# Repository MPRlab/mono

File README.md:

MPR_WORKSPACE
=============

This repository, for the most part, is licensed under GPL V3.0.  This includes any code inside ipython notebooks.  A copy of the GPL V3.0 is available in the file license.txt

This repository is intended to store all code development for the Music Perception and Robotics Lab at WPI.

Currently, it is divided into several different directories:

Old Work:

AudioAnalysis - used for development of a real time pitch and onset detection system

MessagePassing - Test code for message passing via sockets

SharedMemoryTest - Test code for shared memory structure eventually used for leap motion controller

oscpack_1_1_0 - Library code to use for OSC (should have installation code maybe?)

build - All exectuables produced 

New Work:

Algorithmic_Composition_Tools - a directory to place general scripts and tools, like pitch number to western music notation or pitch number to midi output.  

Composition_Workspace_Hughes - Nathan's directory for path planning algorithms and C-Space generator / collision checker

Daughter_Control - directory for eventual software for instrument controllers

Mother_Control - directory for eventual software for motherboard controller

MAX_MSP_MIDI_CONVERTER - max/msp plugin for converting midi to custom osc messages

PAM_CONTROL - directory for old code / test code for pam

PERCUSSION_CONTROL - directory for old code / test code for percussion robot

MISC_DOC - directory for anything that doesn't belong

It also includes the following files:

Makefile - file to make programs from the various directories

README.md - this file

Please note that this repo is very much in progress. Some things that need to be done are the following (but are not limited to)
1) Document current Executables
2) Add Max/MXP plugins to the repo
3) Look into better build system than make

Finally, this repo has programs in a few different langauges and a couple different dependencies.

Languages: C, C++, Python
Dependencies: Jackd (audio analysis), boost (everything), ipython and numpy and scipy (some experimental audio analysis)

The dependencies is not an exhaustive list.  If a program doesn't run, it's probably missing a dependency.
=======
# MPR-lab

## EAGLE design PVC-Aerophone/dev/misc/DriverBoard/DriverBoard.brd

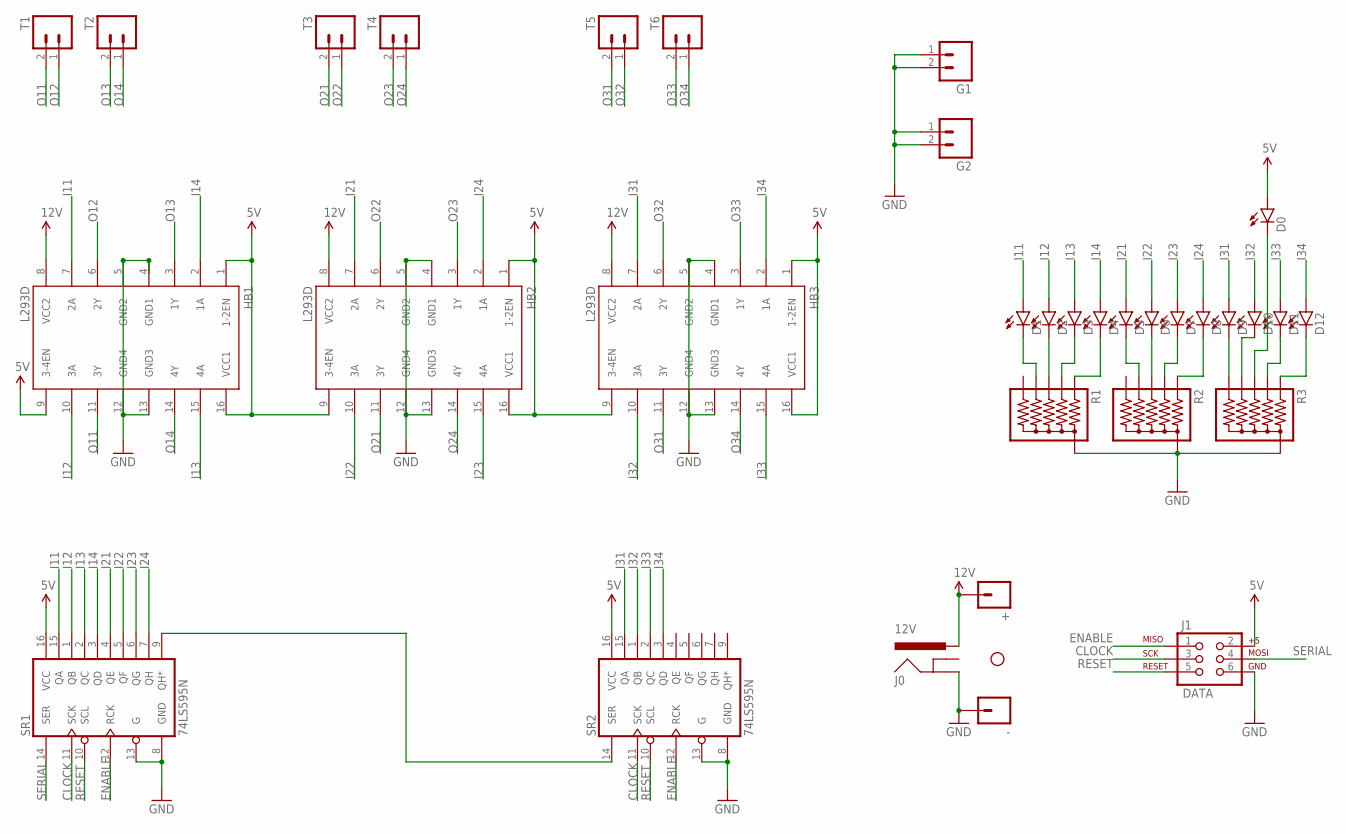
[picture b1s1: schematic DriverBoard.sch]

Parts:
+: M01PTH_NO_SILK_YES_STOP; 1X01_NO_SILK
-: M01PTH_NO_SILK_YES_STOP; 1X01_NO_SILK
D0, D1, D2, D3, D4, D5, D6, D7, D8, D9, D10, D11, D12: LED5MM
G1, G2: M025MM; SCREWTERMINAL-5MM-2
H1: STAND-OFF
HB1, HB2, HB3: L293D; DIL16
J0: 12V; POWER_JACK_PTH_BREAD
J1: DATA; 2X3
R1, R2, R3: RPACK-BUSSED-5-SIP-PTH-5; RPACK-SIP-PTH-5
SR1, SR2: 74LS595N; DIL16
T1, T2, T3, T4, T5, T6: M025MM; SCREWTERMINAL-5MM-2

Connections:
5V: D0.A, HB1.1 (1-2EN), HB1.9 (3-4EN), HB1.16 (VCC1), HB2.1 (1-2EN), HB2.9 (3-4EN), HB2.16 (VCC1), HB3.1 (1-2EN), HB3.9 (3-4EN), HB3.16 (VCC1), J1.2, SR1.16 (VCC), SR2.16 (VCC)
12V: +.1, HB1.8 (VCC2), HB2.8 (VCC2), HB3.8 (VCC2), J0.PWR
CLOCK: J1.3, SR1.11 (SCK), SR2.11 (SCK)
ENABLE: J1.1, SR1.12 (RCK), SR2.12 (RCK)
GND: -.1, G1.1, G1.2, G2.1, G2.2, HB1.4 (GND1), HB1.5 (GND2), HB1.12 (GND4), HB1.13 (GND3), HB2.4 (GND1), HB2.5 (GND2), HB2.12 (GND4), HB2.13 (GND3), HB3.4 (GND1), HB3.5 (GND2), HB3.12 (GND4), HB3.13 (GND3), J0.GND, J1.6, R1.P$1 (1), R2.P$1 (1), R3.P$1 (1), SR1.8 (GND), SR1.13 (G), SR2.8 (GND), SR2.13 (G)
I11: D1.A, HB1.7 (2A), SR1.15 (QA)
I12: D2.A, HB1.10 (3A), SR1.1 (QB)
I13: D3.A, HB1.15 (4A), SR1.2 (QC)
I14: D4.A, HB1.2 (1A), SR1.3 (QD)
I21: D5.A, HB2.7 (2A), SR1.4 (QE)
I22: D6.A, HB2.10 (3A), SR1.5 (QF)
I23: D7.A, HB2.15 (4A), SR1.6 (QG)
I24: D8.A, HB2.2 (1A), SR1.7 (QH)
I31: D9.A, HB3.7 (2A), SR2.15 (QA)
I32: D10.A, HB3.10 (3A), SR2.1 (QB)
I33: D11.A, HB3.15 (4A), SR2.2 (QC)
I34: D12.A, HB3.2 (1A), SR2.3 (QD)
unnamed: D10.K (C), R3.P$5 (5)
unnamed: D0.K (C), R3.P$4 (4)
unnamed: D4.K (C), R1.P$2 (2)
unnamed: D3.K (C), R1.P$3 (3)
unnamed: D2.K (C), R1.P$4 (4)
unnamed: D1.K (C), R1.P$5 (5)
unnamed: D8.K (C), R2.P$2 (2)
unnamed: D7.K (C), R2.P$3 (3)
unnamed: D6.K (C), R2.P$4 (4)
unnamed: D5.K (C), R2.P$5 (5)
unnamed: D12.K (C), R3.P$2 (2)
unnamed: D11.K (C), R3.P$3 (3)
unnamed: D9.K (C), R3.P$6 (6)
unnamed: SR1.9 (QH*), SR2.14 (SER)
O11: HB1.11 (3Y), T1.2
O12: HB1.6 (2Y), T1.1
O13: HB1.3 (1Y), T2.2
O14: HB1.14 (4Y), T2.1
O21: HB2.11 (3Y), T3.2
O22: HB2.6 (2Y), T3.1
O23: HB2.3 (1Y), T4.2
O24: HB2.14 (4Y), T4.1
O31: HB3.11 (3Y), T5.2
O32: HB3.6 (2Y), T5.1
O33: HB3.3 (1Y), T6.2
O34: HB3.14 (4Y), T6.1
RESET: J1.5, SR1.10 (SCL), SR2.10 (SCL)
SERIAL: J1.4, SR1.14 (SER)

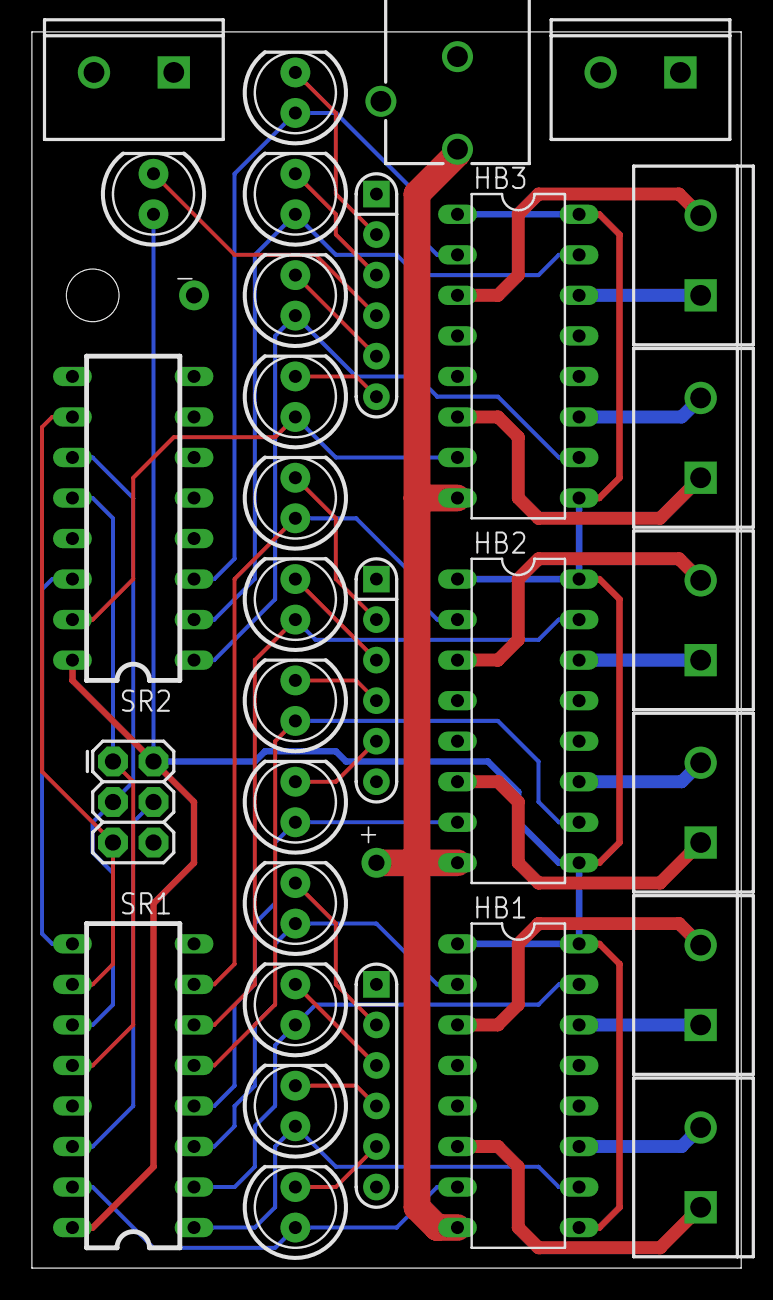
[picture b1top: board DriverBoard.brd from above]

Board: 2 copper layers, 44.5 x 77.5 mm, 34 parts (0 on the bottom side), 45 nets.

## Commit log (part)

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2015-02-25 More complex composition and MAX patch now allows for file to be input more easily
2015-02-25 Interesting composition. Good use of pauses. Better rhyth. Current adding register counting to the code.
2015-02-25 Still having problems exploring register diversity.
2015-02-25 Fixed problems with Airy inclusion. Still noticing some problems with repeated notes. Likely to be related to lack of forward checking in special cases.
2015-02-26 More complex composition. Better use of registers and rhyth. Fixed several bugs with code.
2015-02-26 Much more interesting composition. Added ability to control seed directly from file
2015-02-26 Added ability to choose gaussian distribution. Another composition created.
2015-02-26 Latest composition. Code seems to be fully functional.
2015-03-01 first draft of driver board
2015-03-01 test version that compiles
2015-03-03 transfered changes over to clean clone of repo
2015-03-03 added in proper pitch probabilites
2015-03-03 everything for class today
2015-03-30 starting code for OSC interface between pi and computer
2015-04-04 First push of the complete code for controlling the multi solenoid driver board V1 over serial. OOP. Tested on FluteBot and works for simple header 0x10 with pulse and hold.
2015-04-04 Added a class to control the high current solenoid driver. Code compiles.
2015-04-04 Added two new headers to control the power solenoid.
2015-04-05 New sample song added. Code now parses file and determines which solenoids should be active at any given time appropriately. Works still has to be done to transmit the messages over serial.
2015-04-06 Code is completed. However, has not been tested since it requires the board.
2015-04-06 README file added
2015-04-06 Code should be working. Mapping to solenoids has not been tested.
2015-04-06 Code has a major bug on the serial comparison that impedes serial from sending nonstop. Has been patched but has to be fixed ASAP.
2015-04-07 Changed the sending logic. Such that it now depends on a variable in status class providing proper separation between the com and status class. Also added a last send after song completion to turn of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
2015-04-07 Fixed bug where solenoids would be left ON after completion of song.
2015-04-07 Missing files that were never commited
2015-04-17 Fixed issue of solenoid remaining ON. Created a hack for ensuring song is played properly... Will work on a better solution.
2015-04-17 Program is now correctly managing time without the hack.
2015-04-17 More complex flute song for testing
2015-05-07 added several files I forgot
2015-07-14 Create PAM_code_7
2015-07-14 Create PAM
2015-07-17 Rename PAM_CONTROL/PAM/PAM/PAM_code/PAM_code_1.ino to PAM/PAM_code_1.ino
2015-07-17 Rename PAM_CONTROL/PAM/PAM/PAM_code/PAM_code_2.ino to PAM/PAM_code/PAM_code_2.ino
2015-07-17 Rename PAM_CONTROL/PAM/PAM/PAM_code/PAM_code_3.ino to PAM/PAM_code/PAM_code_3.ino
2015-07-17 Rename PAM_CONTROL/PAM/PAM/PAM_code/PAM_code_4.ino to PAM/PAM_code/PAM_code_4.ino
2015-07-17 Rename PAM/PAM_code_1.ino to PAM/PAM_code/PAM_code_1.ino
2015-07-17 Rename PAM_CONTROL/PAM/PAM/PAM_code/PAM_code_5.ino to PAM/PAM_code/PAM_code_5.ino
2015-07-17 Rename PAM_CONTROL/PAM/PAM/PAM_code/PAM_code_8.ino to PAM/PAM_code/PAM_code_8.ino
2015-07-17 Rename PAM/PAM_code/PAM_code_1.ino to PAM/PAM_code_1.ino
2015-07-17 Rename PAM/PAM_code/PAM_code_2.ino to PAM/PAM_code_2.ino
2015-07-17 Rename PAM/PAM_code/PAM_code_3.ino to PAM/PAM_code_3.ino
2015-07-17 Rename PAM/PAM_code/PAM_code_4.ino to PAM/PAM_code_4.ino
2015-07-17 Rename PAM/PAM_code/PAM_code_5.ino to PAM/PAM_code_5.ino
2015-07-17 Rename PAM/PAM_code/PAM_code_7.ino to PAM/PAM_code_7.ino
2015-07-17 Rename PAM/PAM_code/PAM_code_8.ino to PAM/PAM_code_8.ino
2015-07-17 Rename PAM_CONTROL/PAM/PAM/stepper_motor_interrupts/stepper_motor_interrupts.ino to PAM/stepper_motor_interrupts.ino
2015-07-17 Rename PAM_CONTROL/PAM/PAM/PAMCode-master/sketch_mar20a/PAM.cpp to PAM/Rayce/PAM.cpp
2015-07-17 Rename PAM_CONTROL/PAM/PAM/PAMCode-master/sketch_mar20a/PAM.h to PAM/Rayce/PAM.h
2015-07-17 Rename PAM_CONTROL/PAM/PAM/PAMCode-master/sketch_mar20a/sketch_mar20a.ino to PAM/Rayce/sketch_mar20a.ino
2015-07-18 cleaning up respository
2015-07-20 new code for PAM
    includes checksum
2015-07-21 changes to data reading
2015-07-22 working on serial communications w/ host computer
2015-07-22 uploaded max patches for robot control
2015-07-23 serial object for Max
2015-07-23 updates to patches
2015-07-24 comport object
2015-08-02 removed several hidden files
2015-08-03 beginnings of work on avr-libc code
2015-08-09 more work on converting headers
2015-08-09 some clean up
2015-08-09 more progress
2015-08-17 string robot code
2015-09-15 clean up repo
2015-09-23 updated control software
2015-09-25 remap included
2015-10-01 basic serial communication programs
2015-11-04 changed pins
2016-02-09 upload
2016-02-29 window, colors
    The window wasn’t opening in v3; changed the background color
2016-02-29 cleaned up repo
2016-05-13 multiple channels
    code updated to receive from multiple instruments
2016-05-18 added control for PAM
2016-05-26 added MIDI in
2016-06-05 Added new version of the multisolenoid board code that includes a class for controlling the onboard stepper driver.
2016-06-05 Added a time check between steps so that the motor doesnt step faster than inertial allows. Currently hardcoded in define of steppercontroller file set to 40 milliseconds.
2016-06-05 Added some comments.
2016-06-07 include MIDI velocity control
2016-06-07 organized directory
2016-06-30 added metro
2016-08-09 added pick button and pick delay
2016-10-05 IR sensor sketch
2016-11-13 moved files to other directory
2017-10-13 note on / note off object for MSM 12.3
2017-10-13 sync
2017-11-21 Added project "PVC Aerophone"
2017-11-21 Directory structure updated
2017-11-23 Added gitignore for random files
2017-11-23 Update folder name and contents
2017-11-23 Need to reset PVC Aerophone project
2017-11-23 PVC_Aerophone replaced and should work now
2017-11-23 Directory structure update
2017-11-23 Add RPi setup stuff
2017-11-23 Remove python.gitignore
2017-11-23 Updated gitignore
2017-11-23 Further updated gitignore
2017-11-23 Pls work
2017-11-23 Updated to debug output
2017-11-23 Goodbye setup you clearly are not working
2017-12-05 fix wrong pin being passed to stepper controller
2017-12-06 added new max patch for using stepper on PAM board
2017-12-06 add gitignore
2017-12-06 remove ds_store file in max patch
2017-12-06 removed all ds_store files
2017-12-08 nuts- adding print statements makes it work
2017-12-08 Changes that still aren't working
2017-12-08 disable debug prints
2017-12-08 Testing for the stepper motor and driver
2017-12-14 Max patch working for both uno stepper and board
2017-12-14 debugging stepper controller
2017-12-15 fix an old bug that messed up timing, fix sleeping
2017-12-15 remove print statements in driver
2017-12-15 make sure drivers fully wake up before trying to step
2017-12-15 reduce some code copying
2017-12-15 changes from Professor Barton and additions for testing
2017-12-15 moved to microseconds, but doesn't give better performance
    Tried to decrease the step time, but maybe due to more processing, it
    doesn’t improve the time much.
2017-12-15 some debug statements for checking if stepper is behind
2017-12-15 additional maxpatch changes
2018-01-11 remove broken max patch
2018-01-16 changes for PAM
2018-01-16 removed PAM stepper interface
2018-01-19 add whamola motor controller files at revision 0:f6bb91d80be7
    These are from a remote repository at revision 0:f6bb91d80be7
2018-01-31 fix a bad merge
2018-01-31 deleting .DS_Store again
2018-01-31 properly clear buffer from stepper messages, print debug
2018-01-31 disable header error print
2018-02-02 workaround for extra bytes in power on msg
2018-02-19 update to include other spellings of DS_Store
2018-02-20 really get rid of DS_Store
2018-02-21 fixed routing of PAM picking messages
2018-03-14 increase PWM frequency on solenoids
2018-03-14 disable debug light
2018-03-20 picker, input mapping
    - removed duplicate algorithm for picking
    - implemented direct picking and picking on/off
    - simplified input mapping scheme
2018-03-27 Works again
2018-03-27 changed mapping for PAM and perc
2018-03-31 Mild updates, fixed small bug in serialization of notes
2018-04-02 fixed double picking
2018-05-01 first attempts at building user viewer separately
2018-05-01 fixing some build errors, but linker on NiTE2 still not working
2018-05-04 added Percussive Aerophone testing data
2018-05-09 fixed Cyther mapping
2018-05-09 no change
2018-05-10 Initial aerophone control software
2018-05-12 discovery of instruments over OSC
2018-05-14 osc instrument discovery
2018-05-24 osc max implementation
2018-05-25 fixed damper sustain
    Previously other note-ons would cause the damper to turn off. Now the damper can be held down while playing other notes.
2018-05-25 bug fix
    notes released with pick - fixed
2018-05-25 bug fix
    removed note-offs that were stopping damping
2018-05-28 fixed checksum
2018-05-28 checksum fixed
2018-05-30 added aerophone
2018-05-30 view IP address
2018-05-30 new version
2018-06-01 added external control for damper
2018-07-31 added control of individual pipes for percussive aerophone
2018-10-01 basic serial communication
2018-10-05 velocity control for aerophone implemented
2018-10-05 implemented velocity control on aerophone
2018-10-07 Added new instruments from A18 practicum
    Added parthenope and drum v2
    New presentation mode that can fit more instruments
    Cleaned up and colored wires to make it easier to add to in the future
2018-11-17 Cleaning up repo - moved max patches

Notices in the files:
parts and their libraries:
SparkFun-LED: Licensing: Creative Commons ShareAlike 4.0 International - https://creativecommons.org/licenses/by-sa/4.0
